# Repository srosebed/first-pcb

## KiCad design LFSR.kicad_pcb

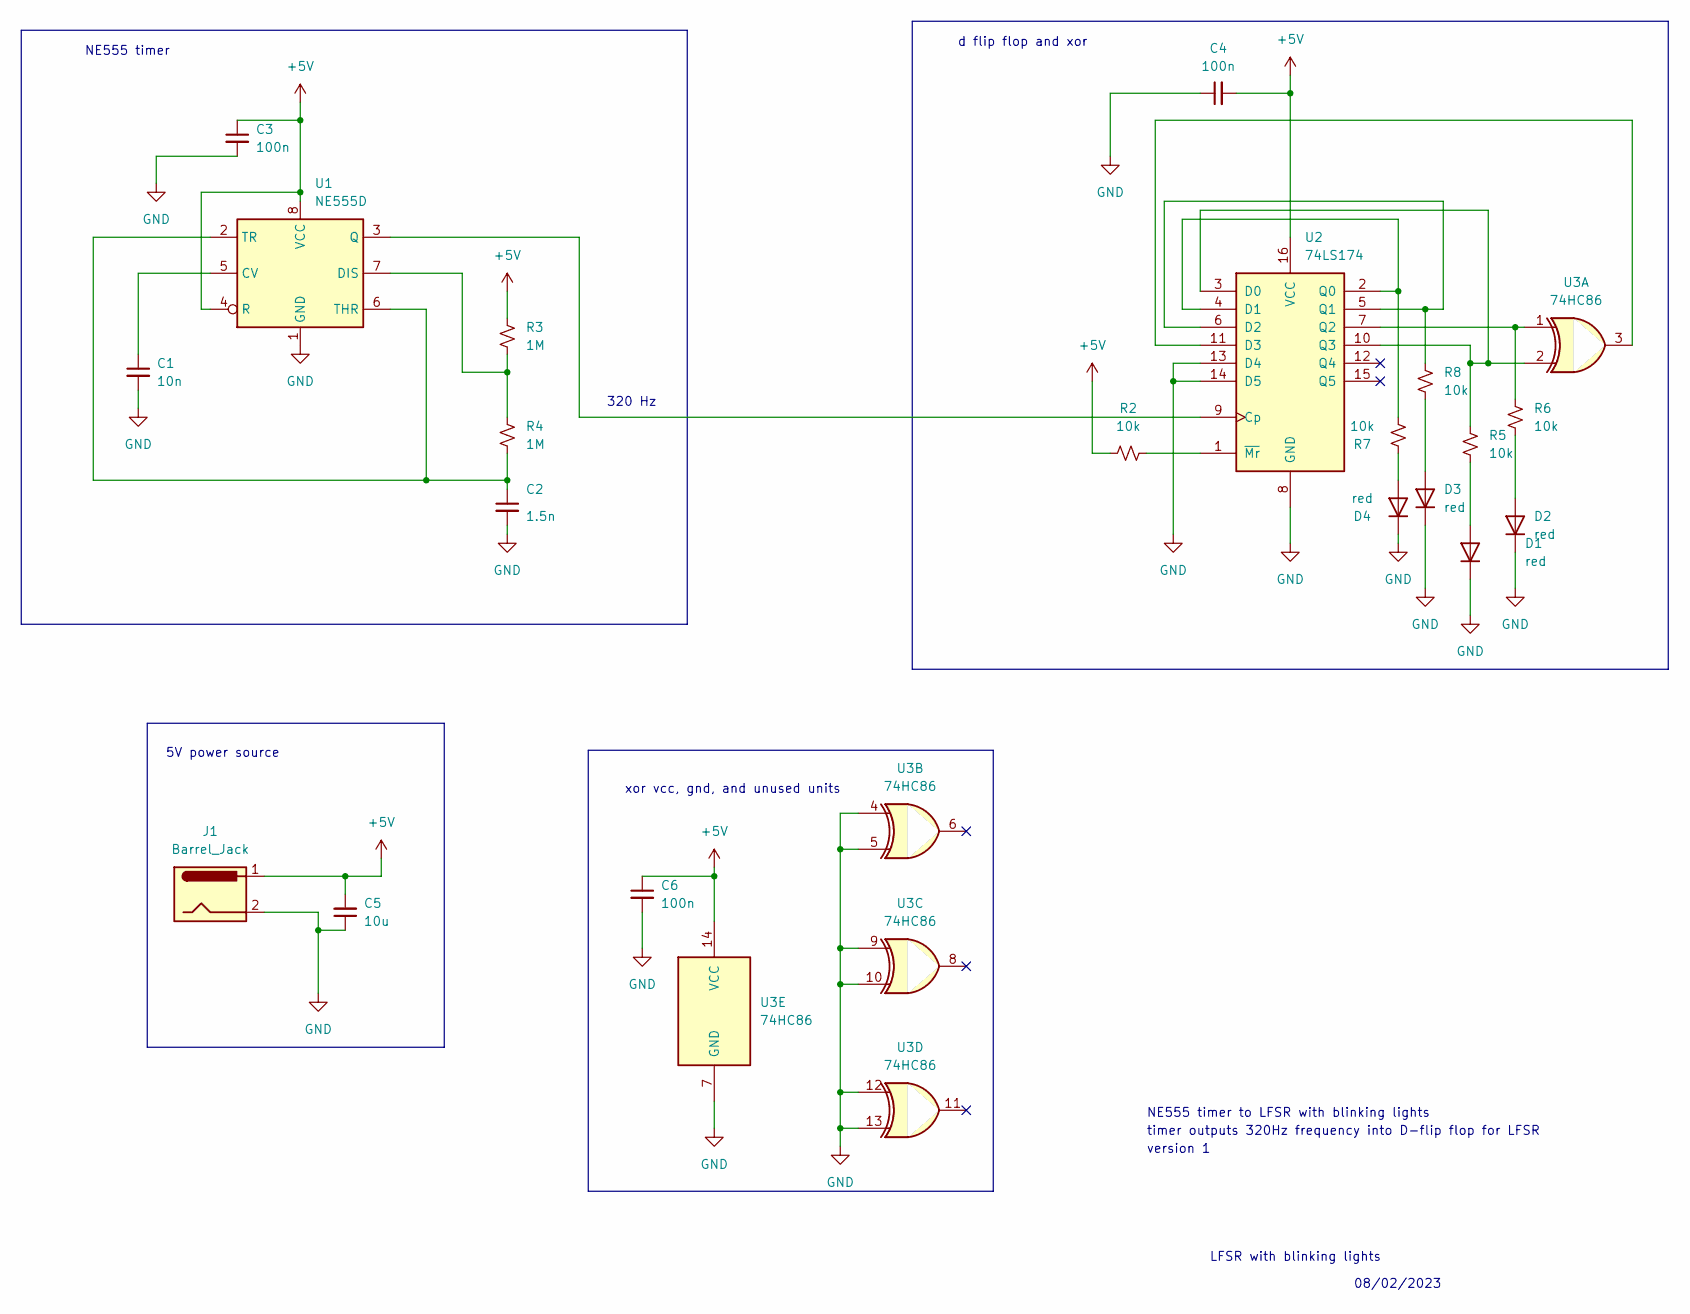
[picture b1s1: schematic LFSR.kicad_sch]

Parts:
C1: 10n; C_1206_3216Metric_Pad1.33x1.80mm_HandSolder
C2: 1.5n; C_1206_3216Metric
C3, C4, C6: 100n; C_1206_3216Metric
C5: 10u; C_1206_3216Metric
D1, D2, D3, D4: red; D_1206_3216Metric
J1: Barrel_Jack; BarrelJack_Wuerth_6941xx301002
R2, R5, R6, R7, R8: 10k; R_1206_3216Metric
R3, R4: 1M; R_1206_3216Metric
U1: NE555D; SOIC-8_3.9x4.9mm_P1.27mm
U2: 74LS174; SOIC-16_3.9x9.9mm_P1.27mm
U3: 74HC86; SOIC-14_3.9x8.7mm_P1.27mm

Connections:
+5V: C3.1, C4.2, C5.2, C6.1, J1.1, R2.1, R3.1, U1.4 (R), U1.8 (VCC), U2.16 (VCC), U3.14 (VCC)
GND: C1.2, C2.2, C3.2, C4.1, C5.1, C6.2, D1.1 (K), D2.1 (K), D3.1 (K), D4.1 (K), J1.2, U1.1 (GND), U2.8 (GND), U2.13 (D4), U2.14 (D5), U3.4, U3.5, U3.7 (GND), U3.9, U3.10, U3.12, U3.13
unnamed: D1.2 (A), R5.2
unnamed: D2.2 (A), R6.2
unnamed: D3.2 (A), R8.2
unnamed: D4.2 (A), R7.1
unnamed: C1.1, U1.5 (CV)
unnamed: R3.2, R4.1, U1.7 (DIS)
unnamed: U1.3 (Q), U2.9 (Cp)
unnamed: C2.1, R4.2, U1.2 (TR), U1.6 (THR)
unnamed: R5.1, U2.3 (D0), U2.10 (Q3), U3.2
unnamed: R7.2, U2.2 (Q0), U2.4 (D1)
unnamed: R8.1, U2.5 (Q1), U2.6 (D2)
unnamed: U2.11 (D3), U3.3
unnamed: R6.1, U2.7 (Q2), U3.1
unnamed: R2.2, U2.1 (~Mr)

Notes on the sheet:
LFSR with blinking lights
NE555 timer to LFSR with blinking lights
timer outputs 320Hz frequency into D-flip flop for LFSR
08/02/2023
xor vcc, gnd, and unused units
5V power source
d flip flop and xor
NE555 timer
320 Hz
version 1

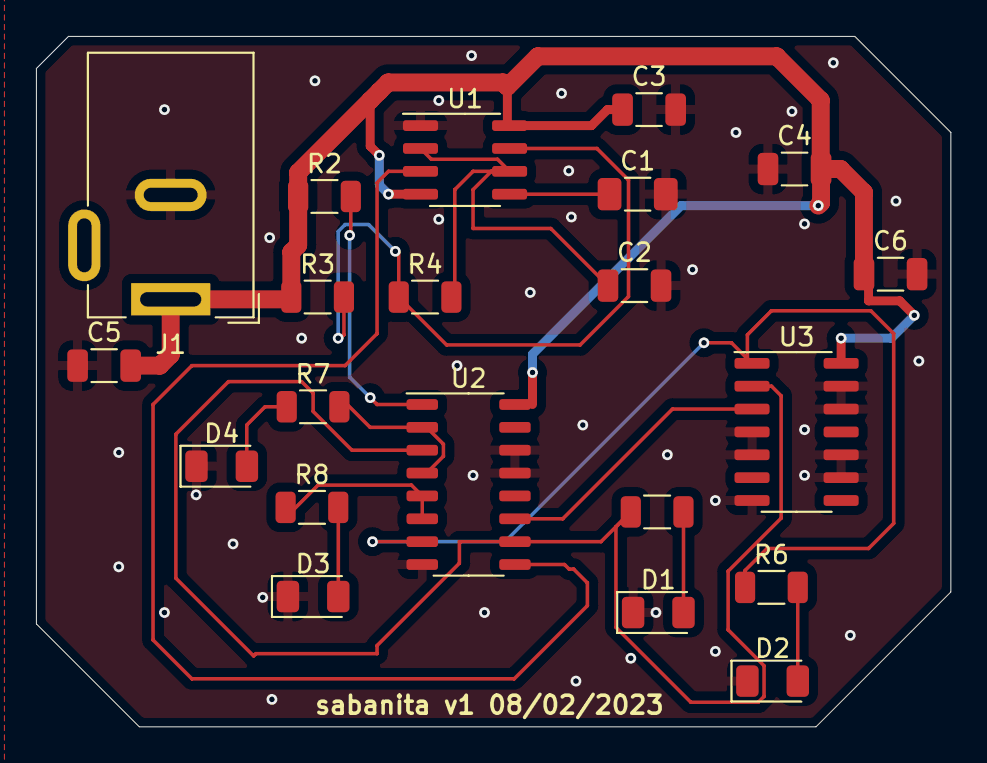
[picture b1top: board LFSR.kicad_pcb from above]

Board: 2 copper layers, 50.8 x 38.4 mm, 21 parts (0 on the bottom side), 16 nets.

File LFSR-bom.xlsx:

Qty | P/NP | Parts | MFR | MPN | Description | Generic | Module | Stock | DIST | DPN | DIST2 | DPN2 | NOTES | ORDER QTY | Order | Current Inventory
1.0 | P | C1 | KYOCERA AVX | KGM05AR71C103KH | SMD 10n capacitor 1206_3216Metric | Y | N/A |  | Digi-Key | 478-KGM05AR71C103KHCT-ND |  |  |  | 2 | 16.0 | 18.0
1.0 | P | C2 | KYOCERA AVX | KGM31BCG1H152JT | SMD 1.5n capacitor 1206_3216Metric | Y | N/A |  | Digi-Key | 478-KGM31BCG1H152JTCT-ND |  |  |  | 2 | 1.0 | 5.0
3.0 | P | C3, C4, C6 | Samsung Electro-Mechanics | CL31B104KCFNNNE | SMD 100n capacitor 1206_3216Metric | Y | N/A |  | Digi-Key | 1276-1151-1-ND |  |  |  | 6
1.0 | P | C5 | Samsung Electro-Mechanics | CL31A106KQHNNNE | SMD 10u capacitor 1206_3216Metric | Y | N/A |  | Digi-Key | 1276-1079-1-ND |  |  |  | 2
4.0 | P | D1, D2, D3, D4 | Visual Communications Company - VCC | CMD15-21VRD/TR8 | SMD red diode 1206_3216Metric | Y | N/A |  | Digi-Key | L62301CT-ND |  |  |  | 8 |  | 19.0
1.0 | P | J1 | SparkFun | PRT-10811 | BarrelJack Connector 6941xx301002 | Y | N/A |  | Mouser | 474-PRT-10811 |  |  |  | 2 |  | 22.0
5.0 | P | R2, R5, R6, R7, R8 | Stackpole Electronics Inc | RNCP1206FTD10K0 | SMD 10k resistor 1026_3216Metric | Y | N/A |  | Digi-Key | RNCP1206FTD10K0CT-ND |  |  |  | 10 | 4.0 | 0.0
2.0 | P | R3, R4 | Rohm Semiconductor | KTR18EZPF1004 | SMD 1M resistor 1206_3216Metric | Y | N/A |  | Digi-Key | RHM1MAICT-ND |  |  |  | 4 | 5.0 | 5.0
1.0 | P | U1 | Texas Instruments | NE555D | NE555D SOIC-8_3.9X4.9mm_P1.27mm | Y | N/A |  | Digi-Key | 296-16792-ND |  |  |  | 2 | 1.0
1.0 | P | U2 | Texas Instruments | SN74LS174D | 74LS174 D-FF SOIC-16W_3.9x9.9mm_P1.27mm | Y | N/A |  | Digi-Key | 296-33971-5-ND |  |  |  | 2 | 0.0
1.0 | P | U3 | Texas Instruments | SN74HC86D | 74HC86 XOR SOIC-14_3.9x8.7mm_P1.27mm | Y | N/A |  | Digi-Key | 296-8374-5-ND |  |  |  | 2 | 2.0 | 2.0
 | P |  |  |  |  |  |  |  |  |  |  |  |  | 0 | 1.0
 | P |  |  |  |  |  |  |  |  |  |  |  |  | 0 | 0.0 | 1.0
 | P |  |  |  |  |  |  |  |  |  |  |  |  | 0 | 2.0 | 1.0
 | P |  |  |  |  |  |  |  |  |  |  |  |  | 0 |  | 0.0
 | P |  |  |  |  |  |  |  |  |  |  |  |  | 0 | 9.0 | 11.0
 | P |  |  |  |  |  |  |  |  |  |  |  |  | 0
 | P |  |  |  |  |  |  |  |  |  |  |  |  | 0
 | P |  |  |  |  |  |  |  |  |  |  |  |  | 0 |  | 5.0
 | P |  |  |  |  |  |  |  |  |  |  |  |  | 0
 | P |  |  |  |  |  |  |  |  |  |  |  |  | 0
 | P |  |  |  |  |  |  |  |  |  |  |  |  | 0 | 5.0
 | P |  |  |  |  |  |  |  |  |  |  |  |  | 0 | 1.0
 | P |  |  |  |  |  |  |  |  |  |  |  |  | 0 | 2.0
 | P |  |  |  |  |  |  |  |  |  |  |  |  | 0 |  | 6.0
 | P |  |  |  |  |  |  |  |  |  |  |  |  | 0 | 1.0
 |  |  |  |  |  |  |  |  |  |  |  |  |  | 0
 |  |  |  |  |  |  |  |  |  |  |  |  |  |  |  | 50.0
 |  |  |  |  |  |  |  |  |  |  |  |  |  | 0

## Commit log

2023-08-10 added three project files for my first pcb
2023-08-10 added bom
